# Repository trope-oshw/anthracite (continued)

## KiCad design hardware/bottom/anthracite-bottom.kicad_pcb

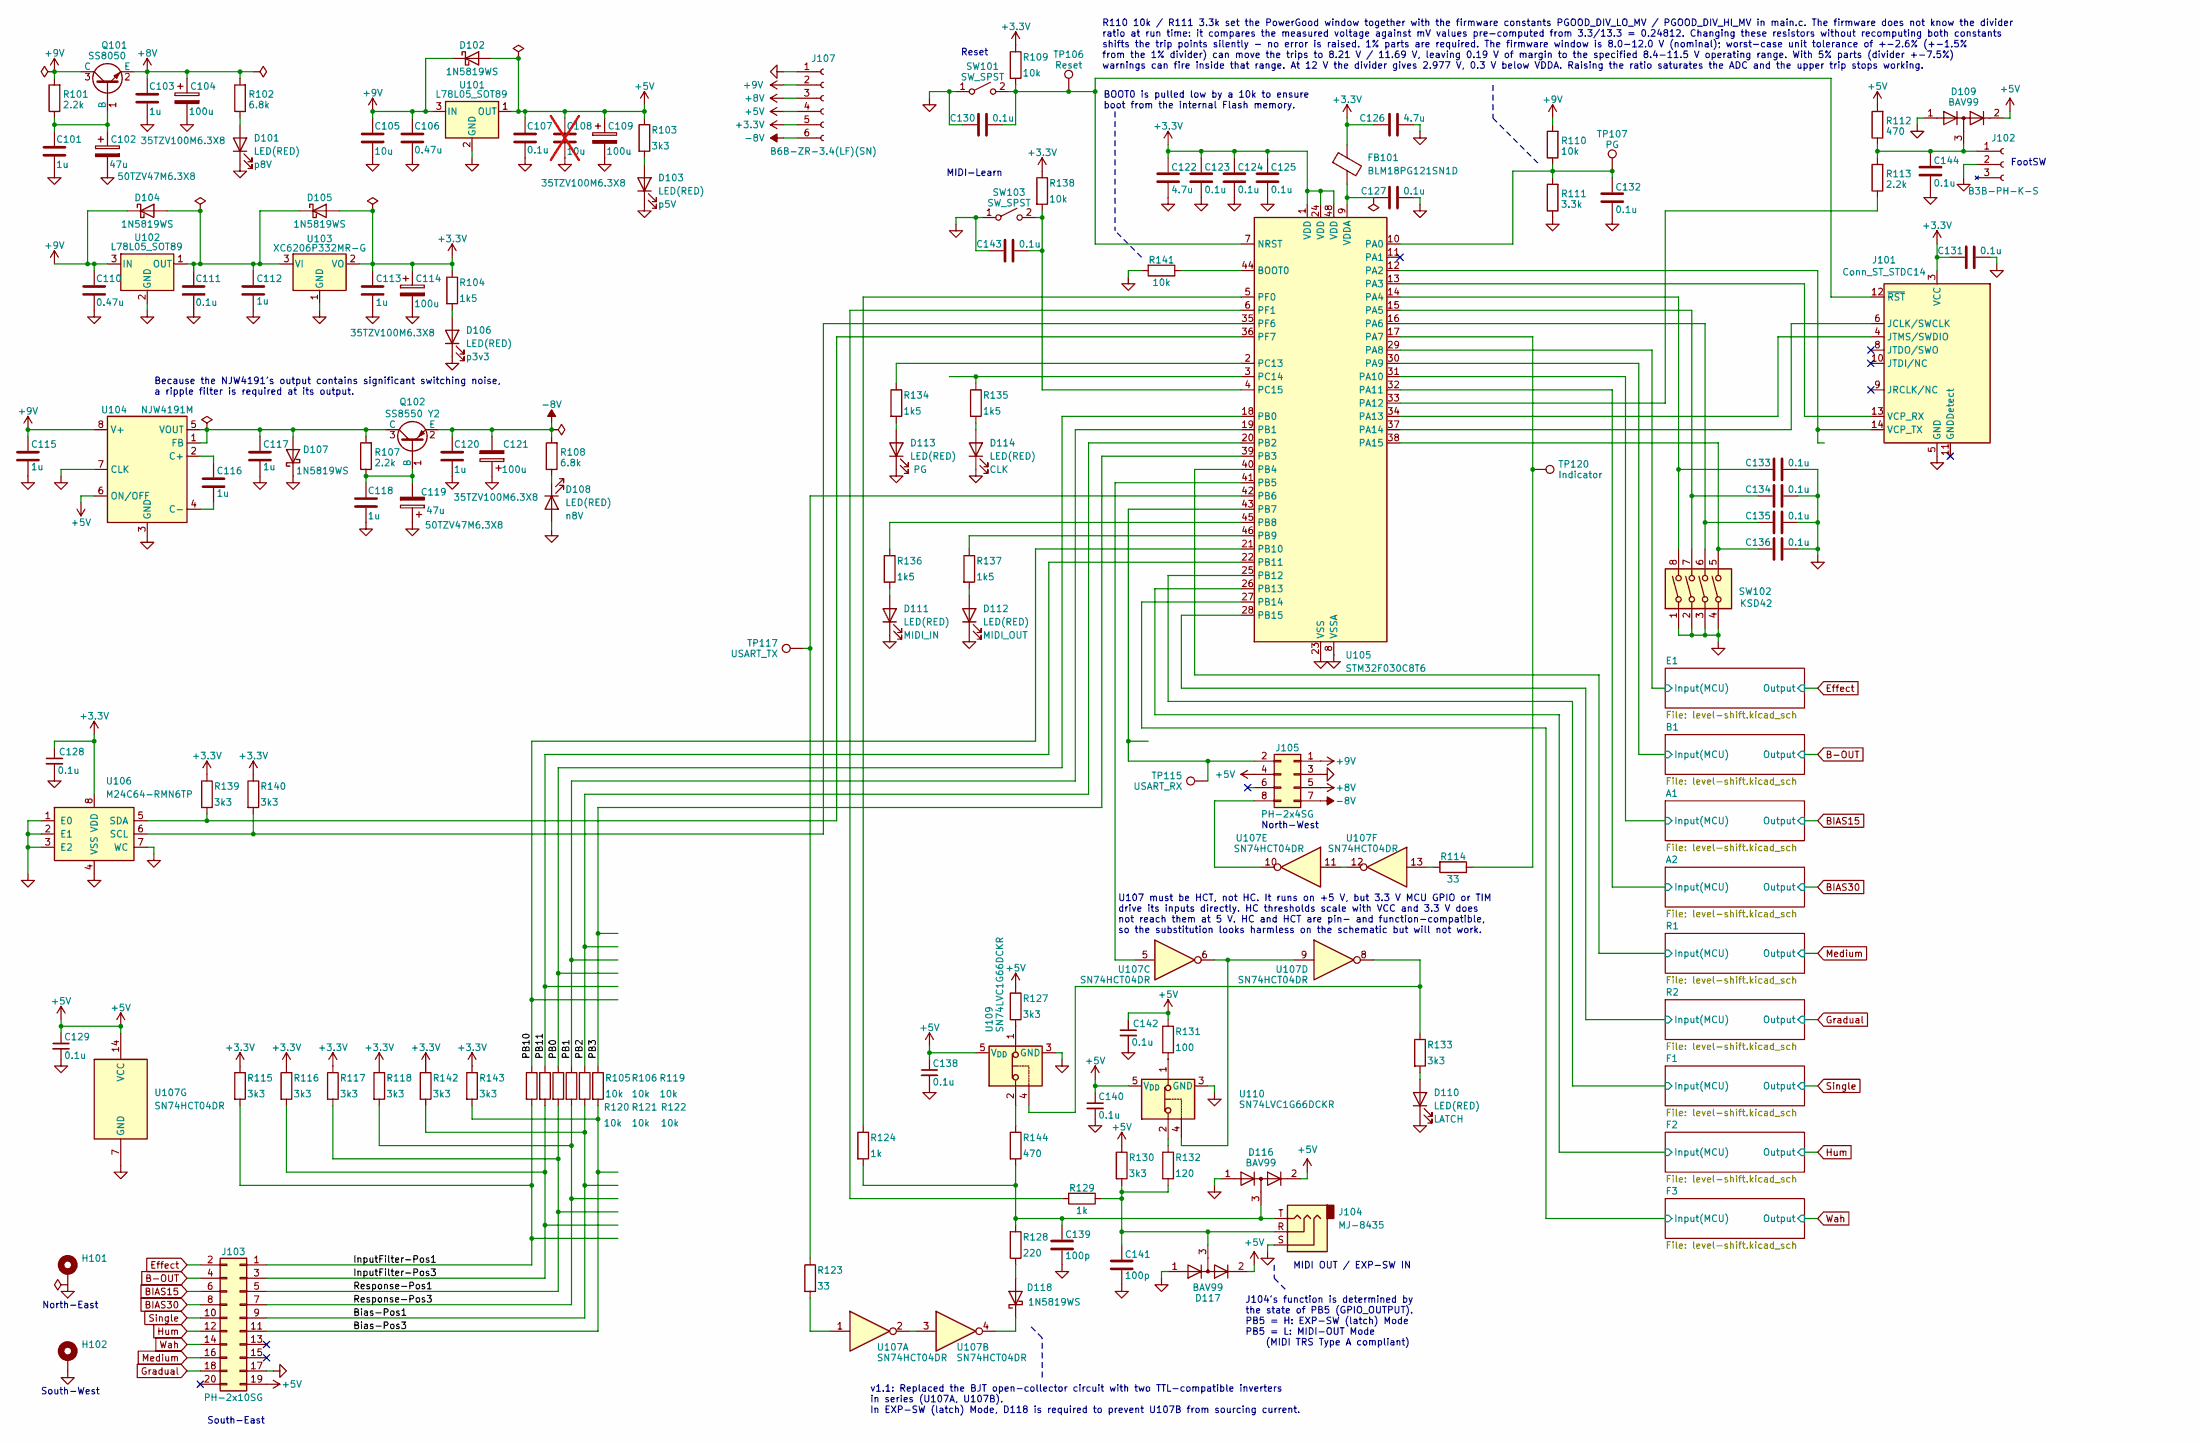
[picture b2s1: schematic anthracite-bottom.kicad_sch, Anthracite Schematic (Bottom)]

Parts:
C101, C103, C112, C113, C115, C116, C117, C118, C120: 1u; C_0805_2012Metric; Tolerance 10%; Voltage 50V; MPN CL21B105KBFNNNE; LCSC C28323
C102, C119: 47u; CP_Rubycon_35TZV100M6.3X8; Tolerance 20%; Voltage 50V; MPN 50TZV47M6.3X8; LCSC C88734
C104, C109, C114, C121: 100u; CP_Rubycon_35TZV100M6.3X8; Tolerance 20%; Voltage 35V; MPN 35TZV100M6.3X8; LCSC C88744
C105: 10u; C_0805_2012Metric; Tolerance 10%; Voltage 25V; LCSC C15850
C106, C110: 0.47u; C_0603_1608Metric; Tolerance 10%; Voltage 25V; LCSC C1623
C107, C111: 0.1u; C_0805_2012Metric; Tolerance 10%; Voltage 50V; LCSC C49678
C108: 10u; C_0805_2012Metric; Tolerance 10%; Voltage 50V; MPN GRM21BR61H106KE43L; LCSC C440198; not fitted
C122, C126: 4.7u; C_0805_2012Metric; Tolerance 10%; Voltage 25V; LCSC C1779
C123, C124, C125, C127, C128, C129, C130, C131, C132, C133, C134, C135, C136, C138, C140, C142, C143, C144: 0.1u; C_0603_1608Metric; Tolerance 10%; Voltage 50V; LCSC C14663
C139, C141: 100p; C_0603_1608Metric; Tolerance 5%; Voltage 50V; LCSC C14858
D101, D103, D106, D108, D110, D111, D112, D113, D114: LED(RED); D_0603_1608Metric_Name; MPN KT-0603R; LCSC C2286
D102, D104, D105, D107, D118: 1N5819WS; D_SOD-323; MPN 1N5819WS; LCSC C191023
D109, D116, D117: BAV99; SOT-23; MPN BAV99,215; LCSC C2500
FB101: BLM18PG121SN1D; L_0603_1608Metric; Tolerance 25%; LCSC C14709
H101, H102: MountingHole_Pad; MountingHole_3.2mm_M3_DIN965_Pad
J101: Conn_ST_STDC14; STDC14_2x07_P1.27mm_Vertical_ST-LINKV3; MPN HX JN1.27-2x7P ZZ H4.9
J102: B3B-PH-K-S; JST_PH_B3B-PH-K_1x03_P2.00mm_Vertical; MPN B3B-PH-K-S(LF)(SN)
J103: PH-2x10SG; PinHeader_2x10_P2.54mm_Vertical; MPN PH-2x10SG
J104: MJ-8435; MPN MJ-8435
J105: PH-2x4SG; PinHeader_2x04_P2.54mm_Vertical; MPN PH-2x4SG
J107: B6B-ZR-3.4(LF)(SN); JST_ZH_B6B-ZR_1x06_P1.50mm_Vertical; MPN B6B-ZR-3.4(LF)(SN)
Q101: SS8050; SOT-23; MPN SS8050(RANGE:200-350); LCSC C2150
Q102: SS8550 Y2; SOT-23; MPN SS8550 Y2(RANGE:200-350); LCSC C8542
R101, R107, R113: 2.2k; R_0603_1608Metric; Tolerance 1%; LCSC C4190
R102, R108: 6.8k; R_0603_1608Metric; Tolerance 1%; LCSC C23212
R103, R133: 3k3; R_0402_1005Metric; Tolerance 1%; LCSC C25890
R104, R134, R135, R136, R137: 1k5; R_0402_1005Metric; Tolerance 1%; LCSC C25867
R105, R106, R109, R119, R120, R121, R122, R138, R141: 10k; R_0402_1005Metric_MiniFont; Tolerance 1%; LCSC C25744
R110: 10k; R_0603_1608Metric; Tolerance 1%; LCSC C25804
R111: 3.3k; R_0603_1608Metric; Tolerance 1%; LCSC C22978
R112: 470; R_0603_1608Metric; Tolerance 1%; LCSC C23179
R114, R123: 33; R_0402_1005Metric_MiniFont; Tolerance 1%; LCSC C25105
R115, R116, R117, R118, R127, R130, R139, R140, R142, R143: 3k3; R_0402_1005Metric_MiniFont; Tolerance 1%; LCSC C25890
R124, R129: 1k; R_0402_1005Metric_MiniFont; Tolerance 1%; LCSC C11702
R128: 220; R_0603_1608Metric; Tolerance 1%; LCSC C22962
R131: 100; R_0603_1608Metric; Tolerance 1%; LCSC C22775
R132: 120; R_0402_1005Metric_MiniFont; Tolerance 1%; LCSC C25079
R144: 470; R_0402_1005Metric; Tolerance 1%; LCSC C25117
SW101, SW103: SW_SPST; TS1088AR02016; MPN TS-1088-AR02016; LCSC C720477
SW102: KSD42; DIP-8_W7.62mm; MPN KSD42
TP106, TP107, TP115, TP117, TP120: TestPoint; TestPoint_Pad_1.5x1.5mm_Label
U101, U102: L78L05_SOT89; SOT-89-3; MPN 78L05G-AB3-R; LCSC C71136
U103: XC6206P332MR-G; SOT-23-3; MPN XC6206P332MR-G; LCSC C5446
U104: NJW4191M; DMP-8_P1.27mm_HandSolder; MPN NJW4191M
U105: STM32F030C8T6; LQFP-48_7x7mm_P0.5mm; MPN STM32F030C8T6; LCSC C23922
U106: M24C64-RMN6TP; SOIC-8_3.9x4.9mm_P1.27mm; MPN M24C64-RMN6TP; LCSC C79988
U107: SN74HCT04DR; SOIC-14_3.9x8.7mm_P1.27mm; MPN SN74HCT04DR; LCSC C6766
U109, U110: SN74LVC1G66DCKR; SOT-353_SC-70-5; MPN SN74LVC1G66DCKR; LCSC C113518

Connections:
+3.3V: C113.1, C114.1, C122.1, C123.1, C124.1, C125.1, C126.1, C128.1, C131.1, D105.2 (A), FB101.1, J101.3 (VCC), J107.5, R104.1, R109.1, R115.1, R116.1, R117.1, R118.1, R138.1, R139.1, R140.1, R142.1, R143.1, U103.2 (VO), U105.1 (VDD), U105.24 (VDD), U105.48 (VDD), U106.8 (VDD)
+5V: C107.1, C108.1, C109.1, C129.1, C138.1, C140.1, C142.1, D102.2 (A), D109.2 (K), D116.2 (K), D117.2 (K), J103.19, J105.4, J107.4, R103.1, R112.2, R127.1, R130.1, R131.1, U101.1 (OUT), U104.6 (ON/OFF), U107.14 (VCC), U109.5 (V_{DD}), U110.5 (V_{DD}); also elsewhere on the board
+8V: C103.1, C104.1, J105.5, J107.3, Q101.2 (E), R102.2; also elsewhere on the board
+9V: C105.1, C106.1, C110.1, C115.1, D102.1 (K), D104.1 (K), J105.1, J107.2, Q101.3 (C), R101.2, R110.2, U101.3 (IN), U102.3 (IN), U104.8 (V+)
-8V: C120.1, C121.2, J105.7, J107.6, Q102.2 (E), R108.2; also elsewhere on the board
/A1/Input(MCU): U105.31 (PA10); also elsewhere on the board
/A2/Input(MCU): U105.32 (PA11); also elsewhere on the board
/B1/Input(MCU): U105.30 (PA9); also elsewhere on the board
/Bias-Pos1: J103.9, R121.2, R142.2
/Bias-Pos3: J103.11, R122.2, R143.2
/E1/Input(MCU): U105.29 (PA8); also elsewhere on the board
/F1/Input(MCU): U105.25 (PB12); also elsewhere on the board
/F2/Input(MCU): U105.26 (PB13); also elsewhere on the board
/F3/Input(MCU): U105.27 (PB14); also elsewhere on the board
/InputFilter-Pos1: J103.1, R105.2, R115.2
/InputFilter-Pos3: J103.3, R106.2, R116.2
/PB0: R119.1, U105.18 (PB0)
/PB1: R120.1, U105.19 (PB1)
/PB2: R121.1, U105.20 (PB2)
/PB3: R122.1, U105.39 (PB3)
/PB10: R105.1, U105.21 (PB10)
/PB11: R106.1, U105.22 (PB11)
/R1/Input(MCU): U105.40 (PB4); also elsewhere on the board
/R2/Input(MCU): U105.28 (PB15); also elsewhere on the board
/Response-Pos1: J103.5, R117.2, R119.2
/Response-Pos3: J103.7, R118.2, R120.2
B-OUT: J103.4; also elsewhere on the board
BIAS15: J103.6; also elsewhere on the board
BIAS30: J103.8; also elsewhere on the board
Effect: J103.2; also elsewhere on the board
GNDPWR: C101.2, C102.2, C103.2, C104.2, C105.2, C106.2, C107.2, C108.2, C109.2, C110.2, C111.2, C112.2, C113.2, C114.2, C115.2, C117.2, C118.2, C119.1, C120.2, C121.1, C122.2, C123.2, C124.2, C125.2, C126.2, C127.2, C128.2, C129.2, C130.1, C131.2, C132.2, C133.2, C134.2, C135.2, C136.2, C138.2, C139.2, C140.2, C141.2, C142.2, C143.1, C144.2, D101.1 (K), D103.1 (K), D106.1 (K), D107.1 (K), D108.2 (A), D109.1 (A), D110.1 (K), D111.1 (K), D112.1 (K), D113.1 (K), D114.1 (K), D116.1 (A), D117.1 (A), H101.1 (1_1), H102.1 (1_1), J101.5 (GND), J101.7 (GND), J102.2, J103.17, J104.S, J105.3, J107.1, R111.1, R141.1, SW101.1 (A), SW102.1, SW102.2, SW102.3, SW102.4, SW103.1 (A), U101.2 (GND), U102.2 (GND), U103.1 (GND), U104.3 (GND), U104.7 (CLK), U105.8 (VSSA), U105.23 (VSS), U105.47 (VSS), U106.1 (E0), U106.2 (E1), U106.3 (E2), U106.4 (VSS), U106.7 (WC), U107.7 (GND), U109.3 (GND), U110.3 (GND); also elsewhere on the board
Gradual: J103.18; also elsewhere on the board
Hum: J103.12; also elsewhere on the board
Medium: J103.16; also elsewhere on the board
unnamed: D101.2 (A), R102.1
unnamed: D103.2 (A), R103.2
unnamed: C111.1, C112.1, D104.2 (A), D105.1 (K), U102.1 (OUT), U103.3 (VI)
unnamed: D106.2 (A), R104.2
unnamed: C117.1, D107.2 (A), Q102.3 (C), R107.2, U104.1 (FB), U104.5 (VOUT)
unnamed: D108.1 (K), R108.1
unnamed: C144.1, D109.3 (COM), J102.1, R112.1, R113.2
unnamed: D110.2 (A), R133.2
unnamed: D111.2 (A), R136.2
unnamed: D112.2 (A), R137.2
unnamed: D113.2 (A), R134.2
unnamed: D114.2 (A), R135.2
unnamed: C139.1, D116.3 (COM), J104.T, R124.2, R128.1, R144.2
unnamed: C141.1, D117.3 (COM), J104.R, R129.2, R130.2, R132.2
unnamed: D118.2 (A), R128.2
unnamed: D118.1 (K), U107.4
unnamed: J101.6 (JCLK/SWCLK), U105.37 (PA14)
unnamed: J101.4 (JTMS/SWDIO), U105.34 (PA13)
unnamed: J101.13 (VCP_RX), U105.13 (PA3)
unnamed: J101.14 (VCP_TX), U105.12 (PA2)
unnamed: C130.2, J101.12 (~RST), R109.2, SW101.2 (B), TP106.1 (1_1), U105.7 (NRST)
unnamed: J105.2, TP115.1 (1_1), U105.43 (PB7)
unnamed: J105.8, U107.10
unnamed: C101.1, C102.1, Q101.1 (B), R101.1
unnamed: C118.1, C119.2, Q102.1 (B), R107.1
unnamed: R114.1, U107.13
unnamed: R123.2, U107.1
unnamed: R127.2, U109.1
unnamed: R131.2, U110.1
unnamed: R132.1, U110.2
unnamed: R133.1, U107.8, U109.4
unnamed: R144.1, U109.2
unnamed: C143.2, R138.2, SW103.2 (B), U105.4 (PC15)
unnamed: C116.1, U104.2 (C+)
unnamed: C116.2, U104.4 (C-)
unnamed: R141.2, U105.44 (BOOT0)
unnamed: C132.1, R110.1, R111.2, TP107.1 (1_1), U105.10 (PA0)
unnamed: C133.1, SW102.8, U105.14 (PA4)
unnamed: C134.1, SW102.7, U105.15 (PA5)
unnamed: C135.1, SW102.6, U105.16 (PA6)
unnamed: R114.2, TP120.1 (1_1), U105.17 (PA7)
unnamed: R113.1, U105.33 (PA12)
unnamed: C136.1, SW102.5, U105.38 (PA15)
unnamed: U105.41 (PB5), U107.5
unnamed: R123.1, TP117.1 (1_1), U105.42 (PB6)
unnamed: R136.1, U105.45 (PB8)
unnamed: R137.1, U105.46 (PB9)
unnamed: R134.1, U105.2 (PC13)
unnamed: R135.1, U105.3 (PC14)
unnamed: R124.1, U105.5 (PF0)
unnamed: R129.1, U105.6 (PF1)
unnamed: R140.2, U105.35 (PF6), U106.6 (SCL)
unnamed: R139.2, U105.36 (PF7), U106.5 (SDA)
unnamed: C127.1, FB101.2, U105.9 (VDDA)
unnamed: U107.2, U107.3
unnamed: U107.6, U107.9, U110.4
unnamed: U107.11, U107.12
Single: J103.10; also elsewhere on the board
Wah: J103.14; also elsewhere on the board

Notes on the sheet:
South-West
R110 10k / R111 3.3k set the PowerGood window together with the firmware constants PGOOD_DIV_LO_MV / PGOOD_DIV_HI_MV in main.c. The firmware does not know the divider ratio at run time: it compares the measured voltage against mV values pre-computed from 3.3/13.3 = 0.24812. Changing these resistors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
BOOT0 is pulled low by a 10k to ensure boot from the internal Flash memory.
MIDI-Learn
Because the NJW4191's output contains significant switching noise, a ripple filter is required at its output.
North-East
South-East
North-West
v1.1: Replaced the BJT open-collector circuit with two TTL-compatible inverters in series (U107A, U107B). In EXP-SW (latch) Mode, D118 is required to prevent U107B from sourcing current.
U107 must be HCT, not HC. It runs on +5 V, but 3.3 V MCU GPIO or TIM drive its inputs directly. HC thresholds scale with VCC and 3.3 V does not reach them at 5 V. HC and HCT are pin- and function-compatible, so the substitution looks harmless on the schematic but will not work.
FootSW
MIDI OUT / EXP-SW IN
Reset
J104's function is determined by the state of PB5 (GPIO_OUTPUT). PB5 = H: EXP-SW (latch) Mode PB5 = L: MIDI-OUT Mode (MIDI TRS Type A compliant)

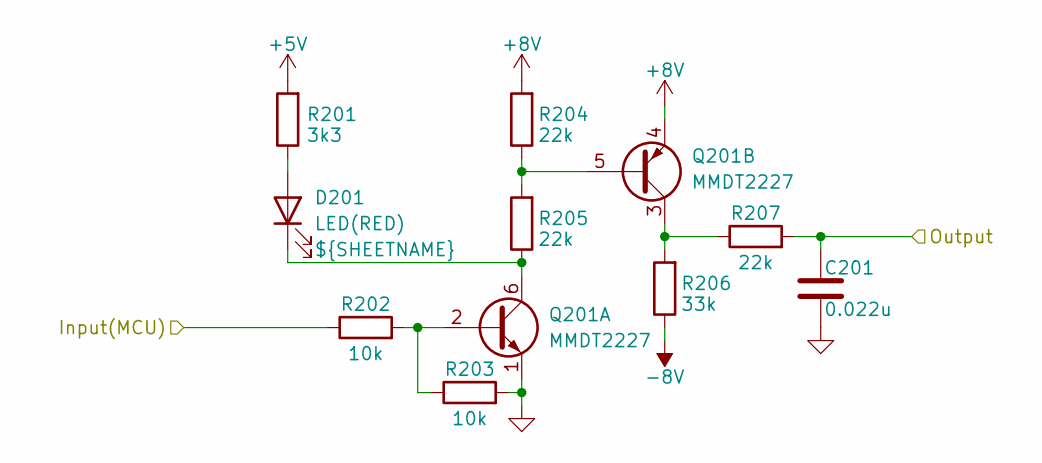
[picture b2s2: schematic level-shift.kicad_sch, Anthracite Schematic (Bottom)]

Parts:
C201: 0.022u; C_0603_1608Metric; Tolerance 10%; Voltage 50V; LCSC C21122
D201: LED(RED); D_0603_1608Metric_Name; MPN KT-0603R; LCSC C2286
Q201: MMDT2227; SOT-363_SC-70-6; MPN MMDT2227; LCSC C41375117
R201: 3k3; R_0402_1005Metric_MiniFont; Tolerance 1%; LCSC C25890
R202, R203: 10k; R_0402_1005Metric_MiniFont; Tolerance 1%; LCSC C25744
R204, R205, R207: 22k; R_0402_1005Metric_MiniFont; Tolerance 1%; LCSC C25768
R206: 33k; R_0402_1005Metric_MiniFont; Tolerance 1%; LCSC C25779

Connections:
+5V: R201.2; also elsewhere on the board
+8V: Q201.4 (E2), R204.2; also elsewhere on the board
-8V: R206.1; also elsewhere on the board
/E1/Input(MCU): R202.1; also elsewhere on the board
Effect: C201.2, R207.2; also elsewhere on the board
GNDPWR: C201.1, Q201.1 (E1), R203.2; also elsewhere on the board
unnamed: D201.2 (A), R201.1
unnamed: D201.1 (K), Q201.6 (C1), R205.1
unnamed: Q201.2 (B1), R202.2, R203.1
unnamed: Q201.5 (B2), R204.1, R205.2
unnamed: Q201.3 (C2), R206.2, R207.1

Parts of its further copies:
C301, C401, C501, C601, C701, C801, C901, C1001: 0.022u; C_0603_1608Metric; Tolerance 10%; Voltage 50V; LCSC C21122
D301, D401, D501, D601, D701, D801, D901, D1001: LED(RED); D_0603_1608Metric_Name; MPN KT-0603R; LCSC C2286
Q301, Q401, Q501, Q601, Q701, Q801, Q901, Q1001: MMDT2227; SOT-363_SC-70-6; MPN MMDT2227; LCSC C41375117
R301, R401, R501, R601, R701, R801, R901, R1001: 3k3; R_0402_1005Metric_MiniFont; Tolerance 1%; LCSC C25890
R302, R303, R402, R403, R502, R503, R602, R603, R702, R703, R802, R803, R902, R903, R1002, R1003: 10k; R_0402_1005Metric_MiniFont; Tolerance 1%; LCSC C25744
R304, R305, R307, R404, R405, R407, R504, R505, R507, R604, R605, R607, R704, R705, R707, R804, R805, R807, R904, R905, R907, R1004, R1005, R1007: 22k; R_0402_1005Metric_MiniFont; Tolerance 1%; LCSC C25768
R306, R406, R506, R606, R706, R806, R906, R1006: 33k; R_0402_1005Metric_MiniFont; Tolerance 1%; LCSC C25779

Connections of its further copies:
+5V: R301.2, R401.2, R501.2, R601.2, R701.2, R801.2, R901.2, R1001.2; also elsewhere on the board
+8V: Q301.4 (E2), Q401.4 (E2), Q501.4 (E2), Q601.4 (E2), Q701.4 (E2), Q801.4 (E2), Q901.4 (E2), Q1001.4 (E2), R304.2, R404.2, R504.2, R604.2, R704.2, R804.2, R904.2, R1004.2; also elsewhere on the board
-8V: R306.1, R406.1, R506.1, R606.1, R706.1, R806.1, R906.1, R1006.1; also elsewhere on the board
/A1/Input(MCU): R402.1; also elsewhere on the board
/A2/Input(MCU): R502.1; also elsewhere on the board
/B1/Input(MCU): R302.1; also elsewhere on the board
/F1/Input(MCU): R602.1; also elsewhere on the board
/F2/Input(MCU): R702.1; also elsewhere on the board
/F3/Input(MCU): R802.1; also elsewhere on the board
/R1/Input(MCU): R902.1; also elsewhere on the board
/R2/Input(MCU): R1002.1; also elsewhere on the board
B-OUT: C301.2, R307.2; also elsewhere on the board
BIAS15: C401.2, R407.2; also elsewhere on the board
BIAS30: C501.2, R507.2; also elsewhere on the board
GNDPWR: C301.1, C401.1, C501.1, C601.1, C701.1, C801.1, C901.1, C1001.1, Q301.1 (E1), Q401.1 (E1), Q501.1 (E1), Q601.1 (E1), Q701.1 (E1), Q801.1 (E1), Q901.1 (E1), Q1001.1 (E1), R303.2, R403.2, R503.2, R603.2, R703.2, R803.2, R903.2, R1003.2; also elsewhere on the board
Gradual: C1001.2, R1007.2; also elsewhere on the board
Hum: C701.2, R707.2; also elsewhere on the board
Medium: C901.2, R907.2; also elsewhere on the board
unnamed: D301.2 (A), R301.1
unnamed: D301.1 (K), Q301.6 (C1), R305.1
unnamed: D401.2 (A), R401.1
unnamed: D401.1 (K), Q401.6 (C1), R405.1
unnamed: D501.2 (A), R501.1
unnamed: D501.1 (K), Q501.6 (C1), R505.1
unnamed: D601.2 (A), R601.1
unnamed: D601.1 (K), Q601.6 (C1), R605.1
unnamed: D701.2 (A), R701.1
unnamed: D701.1 (K), Q701.6 (C1), R705.1
unnamed: D801.2 (A), R801.1
unnamed: D801.1 (K), Q801.6 (C1), R805.1
unnamed: D901.2 (A), R901.1
unnamed: D901.1 (K), Q901.6 (C1), R905.1
unnamed: D1001.2 (A), R1001.1
unnamed: D1001.1 (K), Q1001.6 (C1), R1005.1
unnamed: Q301.2 (B1), R302.2, R303.1
unnamed: Q301.5 (B2), R304.1, R305.2
unnamed: Q301.3 (C2), R306.2, R307.1
unnamed: Q401.2 (B1), R402.2, R403.1
unnamed: Q401.5 (B2), R404.1, R405.2
unnamed: Q401.3 (C2), R406.2, R407.1
unnamed: Q501.2 (B1), R502.2, R503.1
unnamed: Q501.5 (B2), R504.1, R505.2
unnamed: Q501.3 (C2), R506.2, R507.1
unnamed: Q601.2 (B1), R602.2, R603.1
unnamed: Q601.5 (B2), R604.1, R605.2
unnamed: Q601.3 (C2), R606.2, R607.1
unnamed: Q701.2 (B1), R702.2, R703.1
unnamed: Q701.5 (B2), R704.1, R705.2
unnamed: Q701.3 (C2), R706.2, R707.1
unnamed: Q801.2 (B1), R802.2, R803.1
unnamed: Q801.5 (B2), R804.1, R805.2
unnamed: Q801.3 (C2), R806.2, R807.1
unnamed: Q901.2 (B1), R902.2, R903.1
unnamed: Q901.5 (B2), R904.1, R905.2
unnamed: Q901.3 (C2), R906.2, R907.1
unnamed: Q1001.2 (B1), R1002.2, R1003.1
unnamed: Q1001.5 (B2), R1004.1, R1005.2
unnamed: Q1001.3 (C2), R1006.2, R1007.1
Single: C601.2, R607.2; also elsewhere on the board
Wah: C801.2, R807.2; also elsewhere on the board

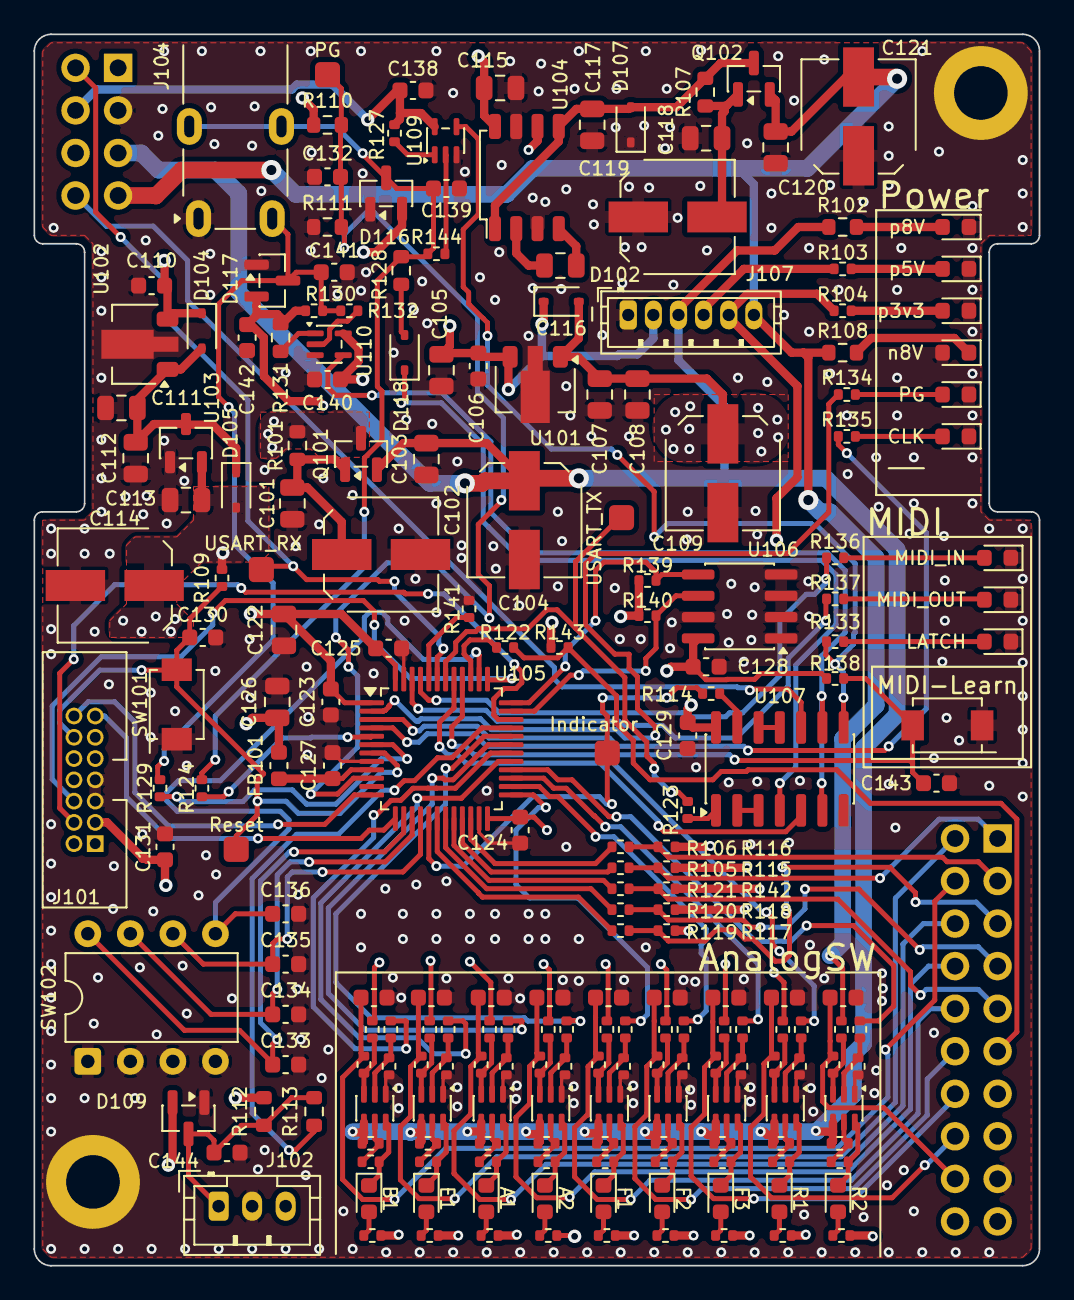
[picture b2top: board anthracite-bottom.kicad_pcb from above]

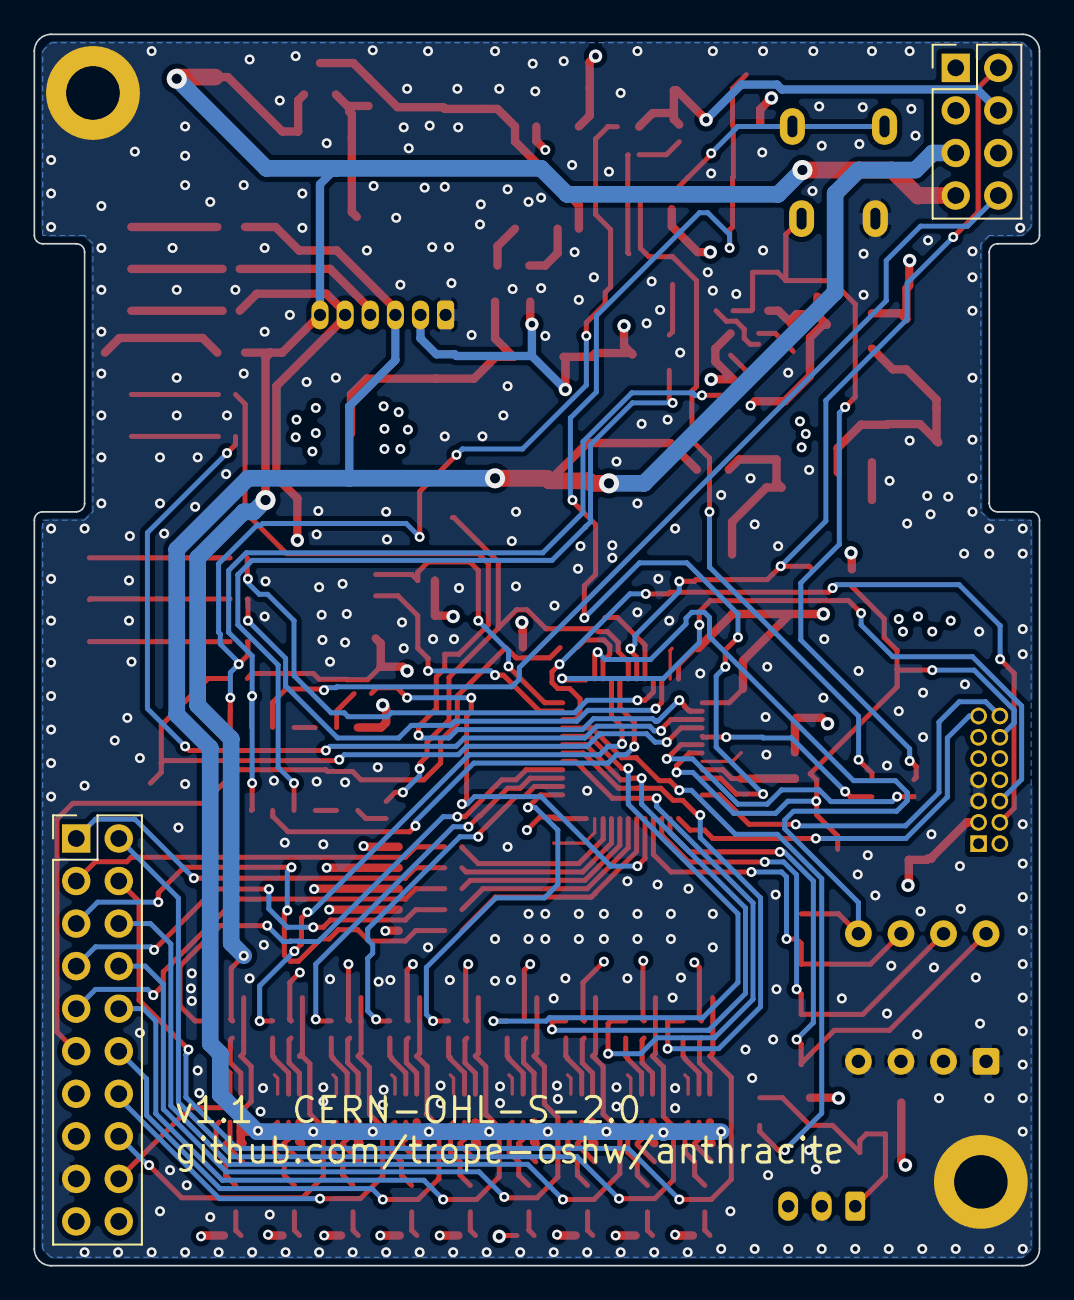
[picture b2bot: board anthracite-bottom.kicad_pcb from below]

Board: 4 copper layers, 60.0 x 73.5 mm, 220 parts (2 on the bottom side), 138 nets.

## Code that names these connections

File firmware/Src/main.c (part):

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   version and stays independent of this. */
#define FW_VERSION "1.1.0"

/* PL9823-F5 (WS2812-compatible) bit-banged output on PA7.
   PA7 -> R114 -> 74HCT04 (two inverters = non-inverting 5V buffer) -> J105-8 -> top R18 -> D12 DIN */
#define WS_PORT   GPIOA
#define WS_PIN    GPIO_PIN_7
#define WS_HIGH() (WS_PORT->BSRR = WS_PIN)
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#define NUM_LEDS  1

#define FOOTSW_DEBOUNCE_MS  50
/* Wait after update_mode_pb5() before reading the latch Tip. PB5 (through U107) closes U109 and
   connects the Tip pull-up (+5V -> R127 3k3 -> U109 -> R144 470); the same PB5 also switches U110
   (MIDI-mode Ring source) and D110. Tip must settle before PF0 is sampled. With the on-board C139
   alone the RC is sub-microsecond; with an external cable's capacitance it stays within a few tens
   of microseconds, so 2ms is ample. 2ms also covers a MIDI byte still shifting out of USART1
   (<= 640us with one byte queued) when DIP-SW3 has just gone OFF. */
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#define IND_BLINK_OFF_MS    100
#define IND_FINAL_OFF_MS    500
#define STARTUP_BLINK_MS    500
#define MIDI_INDICATOR_MS   100   /* PB8/PB9: MIDI activity indicator on-time */
#define LED_FADE_STEP_MS    6     /* PL9823 color fade step interval [ms]; each step closes ~1/3 of the gap */

/* PowerGood ADC (PA0=ADC_IN0) + status LED (PC13)
   Divider R110 10k / R111 3.3k (ratio 3.3/13.3 = 0.24812): 9V in -> 2.23V.
   Warning window: 8.0~12.0V. It encloses the 8.4~11.5V operating range, so the LED does not
   flash inside that range.
   V_DDA is estimated from the VREFINT calibration value to compute the divider voltage [mV];
   PC13 is lit inside the window and blinks at a 0.4s period (50% duty) outside it.
   At 12.0V the divider gives 2.977V, about 0.3V below VDDA (3.28V measured), so the ADC does not saturate. */
#define PGOOD_DIV_LO_MV     1985U  /* Divider voltage for 8.0V (8.0 * 0.24812) */
#define PGOOD_DIV_HI_MV     2977U  /* Divider voltage for 12.0V (12.0 * 0.24812) */
#define PGOOD_POLL_MS       100U   /* ADC sampling interval */
#define PGOOD_BLINK_MS      200U   /* PC13 blink half-period (0.4s period, 50% duty) */
#define ADC_FULL_SCALE      4095U  /* 12bit */
/* VREFINT factory calibration value (taken at VDDA=3.3V). Guarded because bare HAL projects sometimes leave it undefined */
#ifndef VREFINT_CAL_ADDR
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#define VREFINT_CAL_VREF    3300U    /* mV */
#endif

/* ---- VCP debug console (USART2 PA2/PA3, 115200bps, STLINK-V3 VCP) ---- */
#define DBG_LINE_MAX  64   /* RX line buffer; ample for the longest command ("MSEND"/"MRECV" plus 11 bytes) */
#define DBG_TX_MAX    320  /* TX formatting buffer (a snapshot is ~250 chars, plus the three override fields) */

/* ---- PA8 (Effect) falling-edge delay - pop noise countermeasure ----
   On Effect -> Bypass, PA9 (B-OUT) goes High immediately, but only the PA8 (Effect)
   falling edge is delayed by EFFECT_OFF_DELAY_US. The point is to widen the handover
   overlap between Q8 (bypass side) turning on and Q15 (effect side) turning off
   from 0.6ms to 6.4ms, matching the overlap of the Bypass -> Effect direction.
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/* USER CODE BEGIN PV */
static bool effect_active = false;

/* PA8 delayed-OFF state. While armed, TIM14 is running and the ISR drives PA8 Low on expiry */
static volatile bool     effect_off_armed    = false;
static volatile uint16_t effect_off_delay_us = EFFECT_OFF_DELAY_US;
static volatile uint16_t effect_off_count    = 0;  /* Number of delayed OFFs executed (reported by EDLY) */
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/* Toggle switch inputs (all three have pole = GND and an external +3.3V pull-up).
   Pos1 Low = flipped up / Pos3 Low = flipped down / both High = center.
   The schematic net names match the physical layout. */
static GPIO_PinState prev_latch_tip  = GPIO_PIN_SET; /* PF0 */
static GPIO_PinState prev_latch_ring = GPIO_PIN_SET; /* PF1 */
/* Tip debounce for the latch setting: the level being timed and the HAL tick when it was first seen.
   prev_latch_tip holds the accepted level; latch_tip_cand differs from it while a change is pending. */
static GPIO_PinState latch_tip_cand    = GPIO_PIN_SET;
static uint32_t      latch_tip_cand_ms = 0;
static GPIO_PinState prev_bias_pos1  = GPIO_PIN_SET; /* PB2  */
static GPIO_PinState prev_bias_pos3  = GPIO_PIN_SET; /* PB3  */
static GPIO_PinState prev_resp_pos1  = GPIO_PIN_SET; /* PB0  */
static GPIO_PinState prev_resp_pos3  = GPIO_PIN_SET; /* PB1  */
static GPIO_PinState prev_filt_pos1  = GPIO_PIN_SET; /* PB10 */
static GPIO_PinState prev_filt_pos3  = GPIO_PIN_SET; /* PB11 */
static GPIO_PinState prev_footsw     = GPIO_PIN_SET; /* PA12 */

static volatile uint32_t footsw_debounce_ms = 0;

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   The channel follows the same rule as on/off control (DIP-SW4 OFF = fixed CH12 / ON = the MIDI-Learn channel).
   value 0 means "revert": clear the MIDI override and follow the physical toggle again.
   value 1-127 is split into four bands (1-31/32-63/64-95/96-127) to select the state. */
#define TOGGLE_CC_INPUT     83u  /* 0=revert / Single / Hum / Wah / All-OFF */
#define TOGGLE_CC_RESPONSE  84u  /* 0=revert / Steep / Medium / Gradual / (N/A) */
#define TOGGLE_CC_BIAS      85u  /* 0=revert / Center / Offset / Skew / X-Skew */
typedef enum { MIDI_IDLE = 0, MIDI_DATA1, MIDI_DATA2 } midi_state_t;
static volatile uint8_t   midi_rx_buf  = 0;
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static volatile filt_ovr_t filter_override   = FILT_OVR_NONE;
static volatile resp_ovr_t response_override = RESP_OVR_NONE;
static volatile bias_ovr_t bias_override     = BIAS_OVR_NONE;
static volatile uint32_t  midi_indicator_ms     = 0; /* PB8 (MIDI-IN RX) ON time */
static volatile uint32_t  midi_out_indicator_ms = 0; /* PB9 (MIDI-OUT TX) ON time */

/* Periodic MIDI-OUT Active Sensing (0xFE) as a link keep-alive.
   Per the MIDI spec a receiver declares the link dead after 300ms of silence following a 0xFE,
   so send every 250ms for margin. Sent only in MIDI mode (DIP-SW3 ON). MIDI-OUT and the latch input
   share the J104 Tip (PB6 -> R123 -> U107 1->2->3->4 -> D118 -> R128 -> Tip), and no hardware gate
   cuts the driver in latch mode, so any USART1 byte sent then would pull Tip Low and PF0 would read
   it as a footswitch press. The firmware therefore keeps USART1 TX silent in latch mode. */
#define MIDI_AS_INTERVAL_MS 250u
static volatile uint32_t  midi_as_timer_ms = MIDI_AS_INTERVAL_MS;
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static volatile uint16_t  midi_as_hold   = 0;  /* Number of 0xFE delayed by the guard (MSTAT) */
static volatile bool      midi_as_held   = false; /* Whether the current pending 0xFE is already counted */

/* MIDI-Learn (PC15 button + M24C64 EEPROM) */
#define EEPROM_I2C_ADDR  0xA0u   /* M24C64 (E2/E1/E0=GND). WP=GND, so writes are enabled */
#define EEPROM_MEM_ADDR  0x0000u
#define LEARN_MAGIC      0xA5u
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static volatile uint32_t  pc15_debounce_ms = 0;
static GPIO_PinState      prev_pc15 = GPIO_PIN_SET;

/* PowerGood (PA0 ADC / PC13 status LED) */
static volatile bool      power_good        = false; /* true = inside the window */
static volatile uint32_t  pgood_poll_ms     = 0;     /* Countdown to the next measurement */
static volatile uint32_t  pgood_blink_ms    = 0;     /* PC13 blink half-period counter */
static volatile uint8_t   pgood_blink_phase = 0;
/* PowerGood simulation override (for testing): 0=AUTO (measured) / 1=force good / 2=force bad.
   A VCP debug feature (PGSIM command) for checking the main LED PG blink without varying the supply. */
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
/* Debug pins: 14 outputs + 14 inputs. Snapshots are printed in this order */
static const dbg_pin_t dbg_pins[] = {
    { GPIOA, GPIO_PIN_8,  "PA8",  true  },  /* /E1 effect in/out */
    { GPIOA, GPIO_PIN_9,  "PA9",  true  },  /* /B1 bypass out */
    { GPIOA, GPIO_PIN_10, "PA10", true  },  /* /A1 Bias 1.5 */
    { GPIOA, GPIO_PIN_11, "PA11", true  },  /* /A2 Bias 3.0 */
    { GPIOB, GPIO_PIN_4,  "PB4",  true  },  /* /R1 Response Medium */
    { GPIOB, GPIO_PIN_12, "PB12", true  },  /* /F1 Filter Single */
    { GPIOB, GPIO_PIN_13, "PB13", true  },  /* /F2 Filter Hum */
    { GPIOB, GPIO_PIN_14, "PB14", true  },  /* /F3 Filter Wah */
    { GPIOB, GPIO_PIN_15, "PB15", true  },  /* /R2 Response Gradual */
    { GPIOB, GPIO_PIN_5,  "PB5",  true  },  /* Latch/MIDI mode: H = Tip pull-up (U109) + D110, L = Ring source (U110) */
    { GPIOB, GPIO_PIN_8,  "PB8",  true  },  /* MIDI-IN activity LED */
    { GPIOB, GPIO_PIN_9,  "PB9",  true  },  /* MIDI-OUT activity LED */
    { GPIOC, GPIO_PIN_13, "PC13", true  },  /* PowerGood status LED */
    { GPIOC, GPIO_PIN_14, "PC14", true  },  /* Heartbeat LED */
    { GPIOA, GPIO_PIN_4,  "PA4",  false },  /* DIP-SW1 */
    { GPIOA, GPIO_PIN_5,  "PA5",  false },  /* DIP-SW2 */
    { GPIOA, GPIO_PIN_6,  "PA6",  false },  /* DIP-SW3 */
    { GPIOA, GPIO_PIN_15, "PA15", false },  /* DIP-SW4 */
    { GPIOA, GPIO_PIN_12, "PA12", false },  /* Footswitch */
    { GPIOB, GPIO_PIN_0,  "PB0",  false },  /* Response Pos1 */
    { GPIOB, GPIO_PIN_1,  "PB1",  false },  /* Response Pos3 */
    { GPIOB, GPIO_PIN_2,  "PB2",  false },  /* Bias Pos1 */
    { GPIOB, GPIO_PIN_3,  "PB3",  false },  /* Bias Pos3 */
    { GPIOB, GPIO_PIN_10, "PB10", false },  /* Filter Pos1 */
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
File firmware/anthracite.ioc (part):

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Mcu.Name=STM32F030C8Tx
Mcu.Package=LQFP48
Mcu.UserName=STM32F030C8Tx
PA0.Mode=IN0
PA0.Signal=ADC_IN0
PA10.Signal=GPIO_Output
PA11.Signal=GPIO_Output
PA12.Signal=GPIO_Input
PA13.Mode=Serial_Wire
PA13.Signal=SYS_SWDIO
PA14.Mode=Serial_Wire
PA14.Signal=SYS_SWCLK
PA15.GPIOParameters=GPIO_PuPd
PA15.GPIO_PuPd=GPIO_PULLUP
PA15.Signal=GPIO_Input
PA2.Mode=Asynchronous
PA2.Signal=USART2_TX
PA3.Mode=Asynchronous
PA3.Signal=USART2_RX
PA4.GPIOParameters=GPIO_PuPd
PA4.GPIO_PuPd=GPIO_PULLUP
PA4.Signal=GPIO_Input
PA5.GPIOParameters=GPIO_PuPd
PA5.GPIO_PuPd=GPIO_PULLUP
PA5.Signal=GPIO_Input
PA6.GPIOParameters=GPIO_PuPd
PA6.GPIO_PuPd=GPIO_PULLUP
PA6.Signal=GPIO_Input
PA7.Signal=S_TIM14_CH1
PA8.Signal=GPIO_Output
PA9.Signal=GPIO_Output
PB0.Signal=GPIO_Input
PB1.Signal=GPIO_Input
PB10.Signal=GPIO_Input
PB11.Signal=GPIO_Input
PB12.Signal=GPIO_Output
PB13.Signal=GPIO_Output
PB14.Signal=GPIO_Output
PB15.Signal=GPIO_Output
PB2.Signal=GPIO_Input
PB3.Signal=GPIO_Input
PB4.Signal=GPIO_Output
PB5.Signal=GPIO_Output
PB6.Mode=Asynchronous
PB6.Signal=USART1_TX
PB7.Mode=Asynchronous
PB7.Signal=USART1_RX
PB8.Signal=GPIO_Output
PB9.Signal=GPIO_Output
PC13.Signal=GPIO_Output
PC14-OSC32_IN.Signal=GPIO_Output
PC15-OSC32_OUT.Signal=GPIO_Input
PF0-OSC_IN.Signal=GPIO_Input
PF1-OSC_OUT.Signal=GPIO_Input
PF6.Mode=I2C
PF6.Signal=I2C2_SCL
PF7.Mode=I2C
PF7.Signal=I2C2_SDA
RCC.SYSCLKFreq_VALUE=48000000
RCC.SYSCLKSource=RCC_SYSCLKSOURCE_PLLCLK
board=custom
